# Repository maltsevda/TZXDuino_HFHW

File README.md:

# Описание

Это *железная* часть проекта [TZXDuino_HF](https://github.com/maltsevda/TZXDuino_HF). Для работы с проектом, требуется программа [KiCad](https://www.kicad.org/). Если нет желания с ней возиться, то в Release'ах есть готовые gerber файлы. Они точно подходят для JLCPCB, но скорее всего подойдут и для других производителей плат.

Чуть подробнее о проекте написано в [статье на habr.com](https://habr.com/ru/post/590403/).

# Необходимые компоненты

### • Arduino Nano ver. 3.0

Я рекомендую поискать вариант с USB Type-C разъемом. На будущее. Например, подойдет [такой вариант с Aliexpress](https://aliexpress.ru/item/32788387125.html).

### • LCD 1602

Подойдет любой вариант без I2C модуля. Искать в магазине по ключевым словам: `LCD 1602`. Варианты без русской локализации стоят дешево, поэтому советую их. Я использовал [такой модуль](https://aliexpress.ru/item/32500978679.html).

### • Micro SD Card Reader

Настоящее название этого модуля: `Micro SD TF Card Memory Shield Module` и оригинал можно купить [тут](https://electropeak.com/micro-sd-tf-card-adapter-module). Перед покупкой убедитесь, что распиновка совпадает с платой. Свой модуль я покупал [на Алике](https://aliexpress.ru/item/32523546123.html).

### • Кнопки

Подойдут любые кнопки для механической клавиатуры. Например, Cherry MX или их клоны. И, конечно, keycaps'ы для них. Тут советовать не буду, у каждого свои предпочтения. Нужно 4 штуки.

### • Разъем 3.5mm Headphone Jack

Я крайне рекомендую брать [разъемы у этого продавца](https://aliexpress.ru/item/32819338639.html), потому что размеры на плате подогнаны именно под них. Если будете покупать другой вариант, возможно, придется немного модифицировать плату.

### • Резистор

Нужен один резистор для настройки контрастности дисплея. Его номинал зависит от дисплея, в моем случае - это 1 кОм. Подобрать номинал можно при помощи подстроечного резистора.

### • Гребенки

Как минимум 2 гребенки по 40 контактов. Но лучше взять с запасом. Искать в магазине по ключевым словам: `40 pin single row`. Я покупал [желтый вариант](https://aliexpress.ru/item/33012665900.html).

# Советы по сборке и пайке

Перед пайкой я рекомендую проверить загрузчик на Arduino Nano и, если стоит старый `Old Bootloader`, то обновить его. В последствии его обновить можно будет только разомкнув перемычки MISO, MOSI и SCK.

Припоем замыкаем перемычки MOSI, MISO и SCK.

У гребенок на Arduino Nano и LCD 1602 пластиковую часть снимать не надо. А вот модуль SD-карты должен плотно прилегать к плате, поэтому пластиковую часть надо аккуратно снять.

Если у ваших кнопок нет направляющих (маленьких пластиковых штырьков по бокам от основной пимпочки), то уплотнить и выровнять кнопки можно при помощи небольших кусочков изоленты.

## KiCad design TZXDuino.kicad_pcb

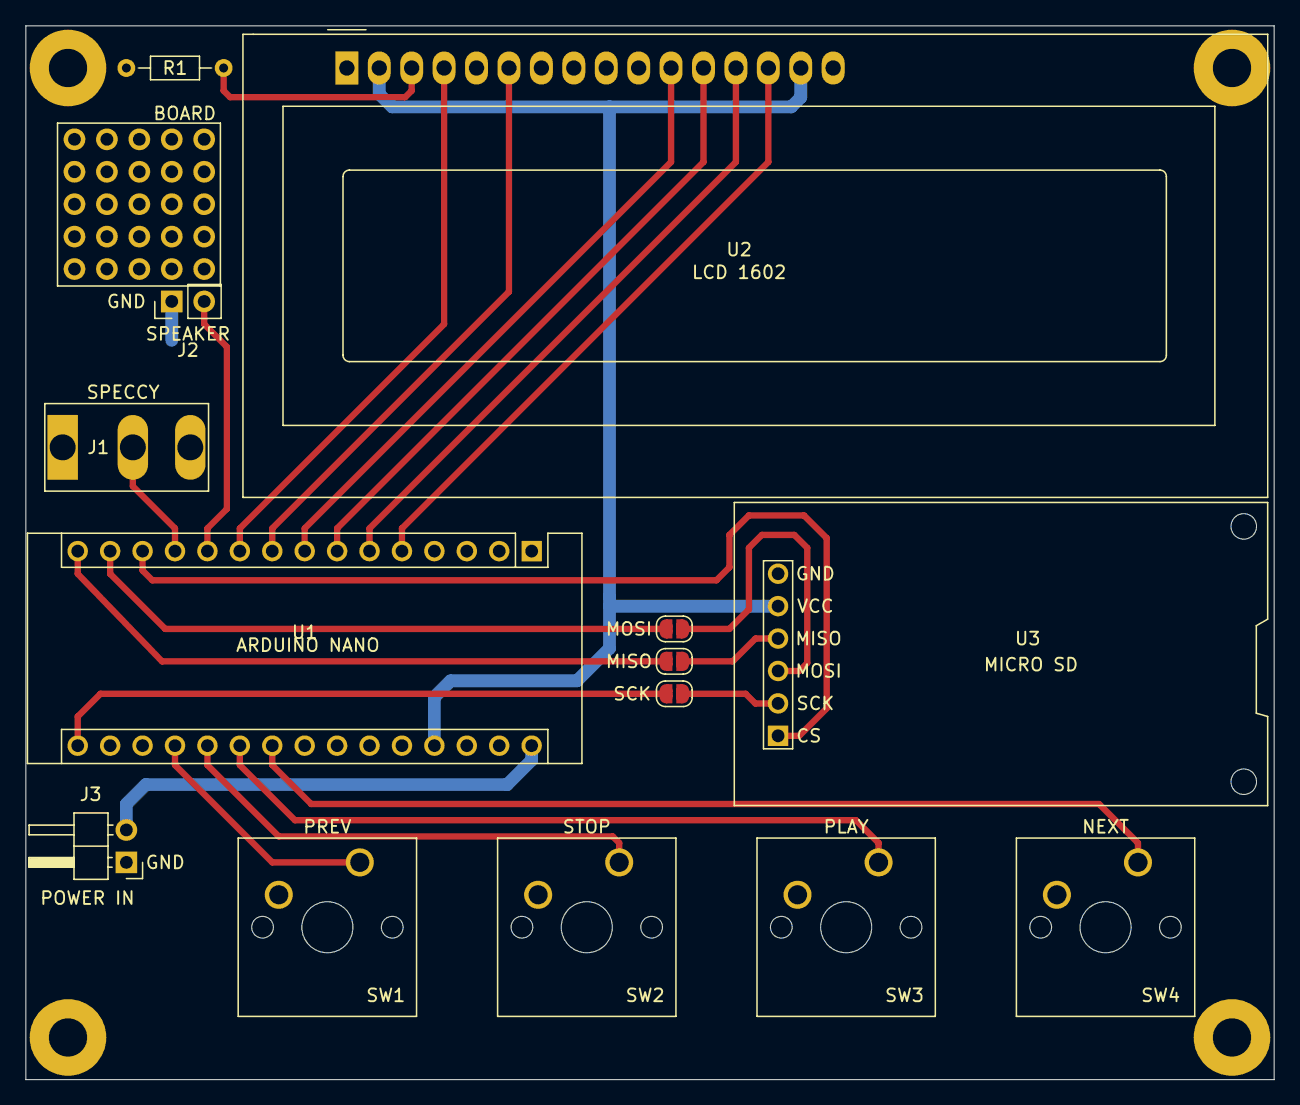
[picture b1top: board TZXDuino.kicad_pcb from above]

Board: 2 copper layers, 97.8 x 82.5 mm, 19 parts (0 on the bottom side), 20 nets.

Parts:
BOARD: PROTOBOARD; ProtoBoard
H1, H2, H3, H4: MountingHole; MountingHole_3mm_Pad
J1: SPECCY; PJ-316
J2: SPEAKER; PinHeader_1x02_P2.54mm_Vertical
J3: POWER IN; PinHeader_1x02_P2.54mm_Horizontal
MISO: SolderJumper-2_P1.3mm_Open_RoundedPad1.0x1.5mm
MOSI: SolderJumper-2_P1.3mm_Open_RoundedPad1.0x1.5mm
R1: 1K; R_Axial_DIN0204_L3.6mm_D1.6mm_P7.62mm_Horizontal
SCK: SolderJumper-2_P1.3mm_Open_RoundedPad1.0x1.5mm
SW1, SW2, SW3, SW4: CHERRY MX; SW_Cherry_MX_1.00u_PCB
U1: ARDUINO NANO; Arduino_Nano
U2: LCD 1602; LCD1602
U3: Catalex_Micro_SD

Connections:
+5V: U1.27, U2.2, U2.15, U3.5
A0: SW1.1, U1.19
A1: SW2.1, U1.20
A2: SW3.1, U1.21
A3: SW4.1, U1.22
CS: U1.13, U3.1
D2: U1.5, U2.14
D3: U1.6, U2.13
D4: U1.7, U2.12
D5: U1.8, U2.11
D6: U1.9, U2.6
D7: U1.10, U2.4
D8: J2.2, U1.11
D9: J1.T, U1.12
GND: J1.S, J2.1, J3.1, R1.2, SW1.2, SW2.2, SW3.2, SW4.2, U1.4, U1.29, U2.1, U2.5, U2.16, U3.6
MISO: MISO.1, MISO.2, U1.15, U3.4
MOSI: MOSI.1, MOSI.2, U1.14, U3.3
unnamed: J3.2, U1.30
unnamed: R1.1, U2.3
SCK: SCK.1, SCK.2, U1.16, U3.2

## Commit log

2021-10-10 First upload
2021-11-28 Readme updated
